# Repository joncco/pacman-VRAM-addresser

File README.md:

This is a reproduction of the VRAM Addresser board used in Midway's Pac-Man arcade PCB.

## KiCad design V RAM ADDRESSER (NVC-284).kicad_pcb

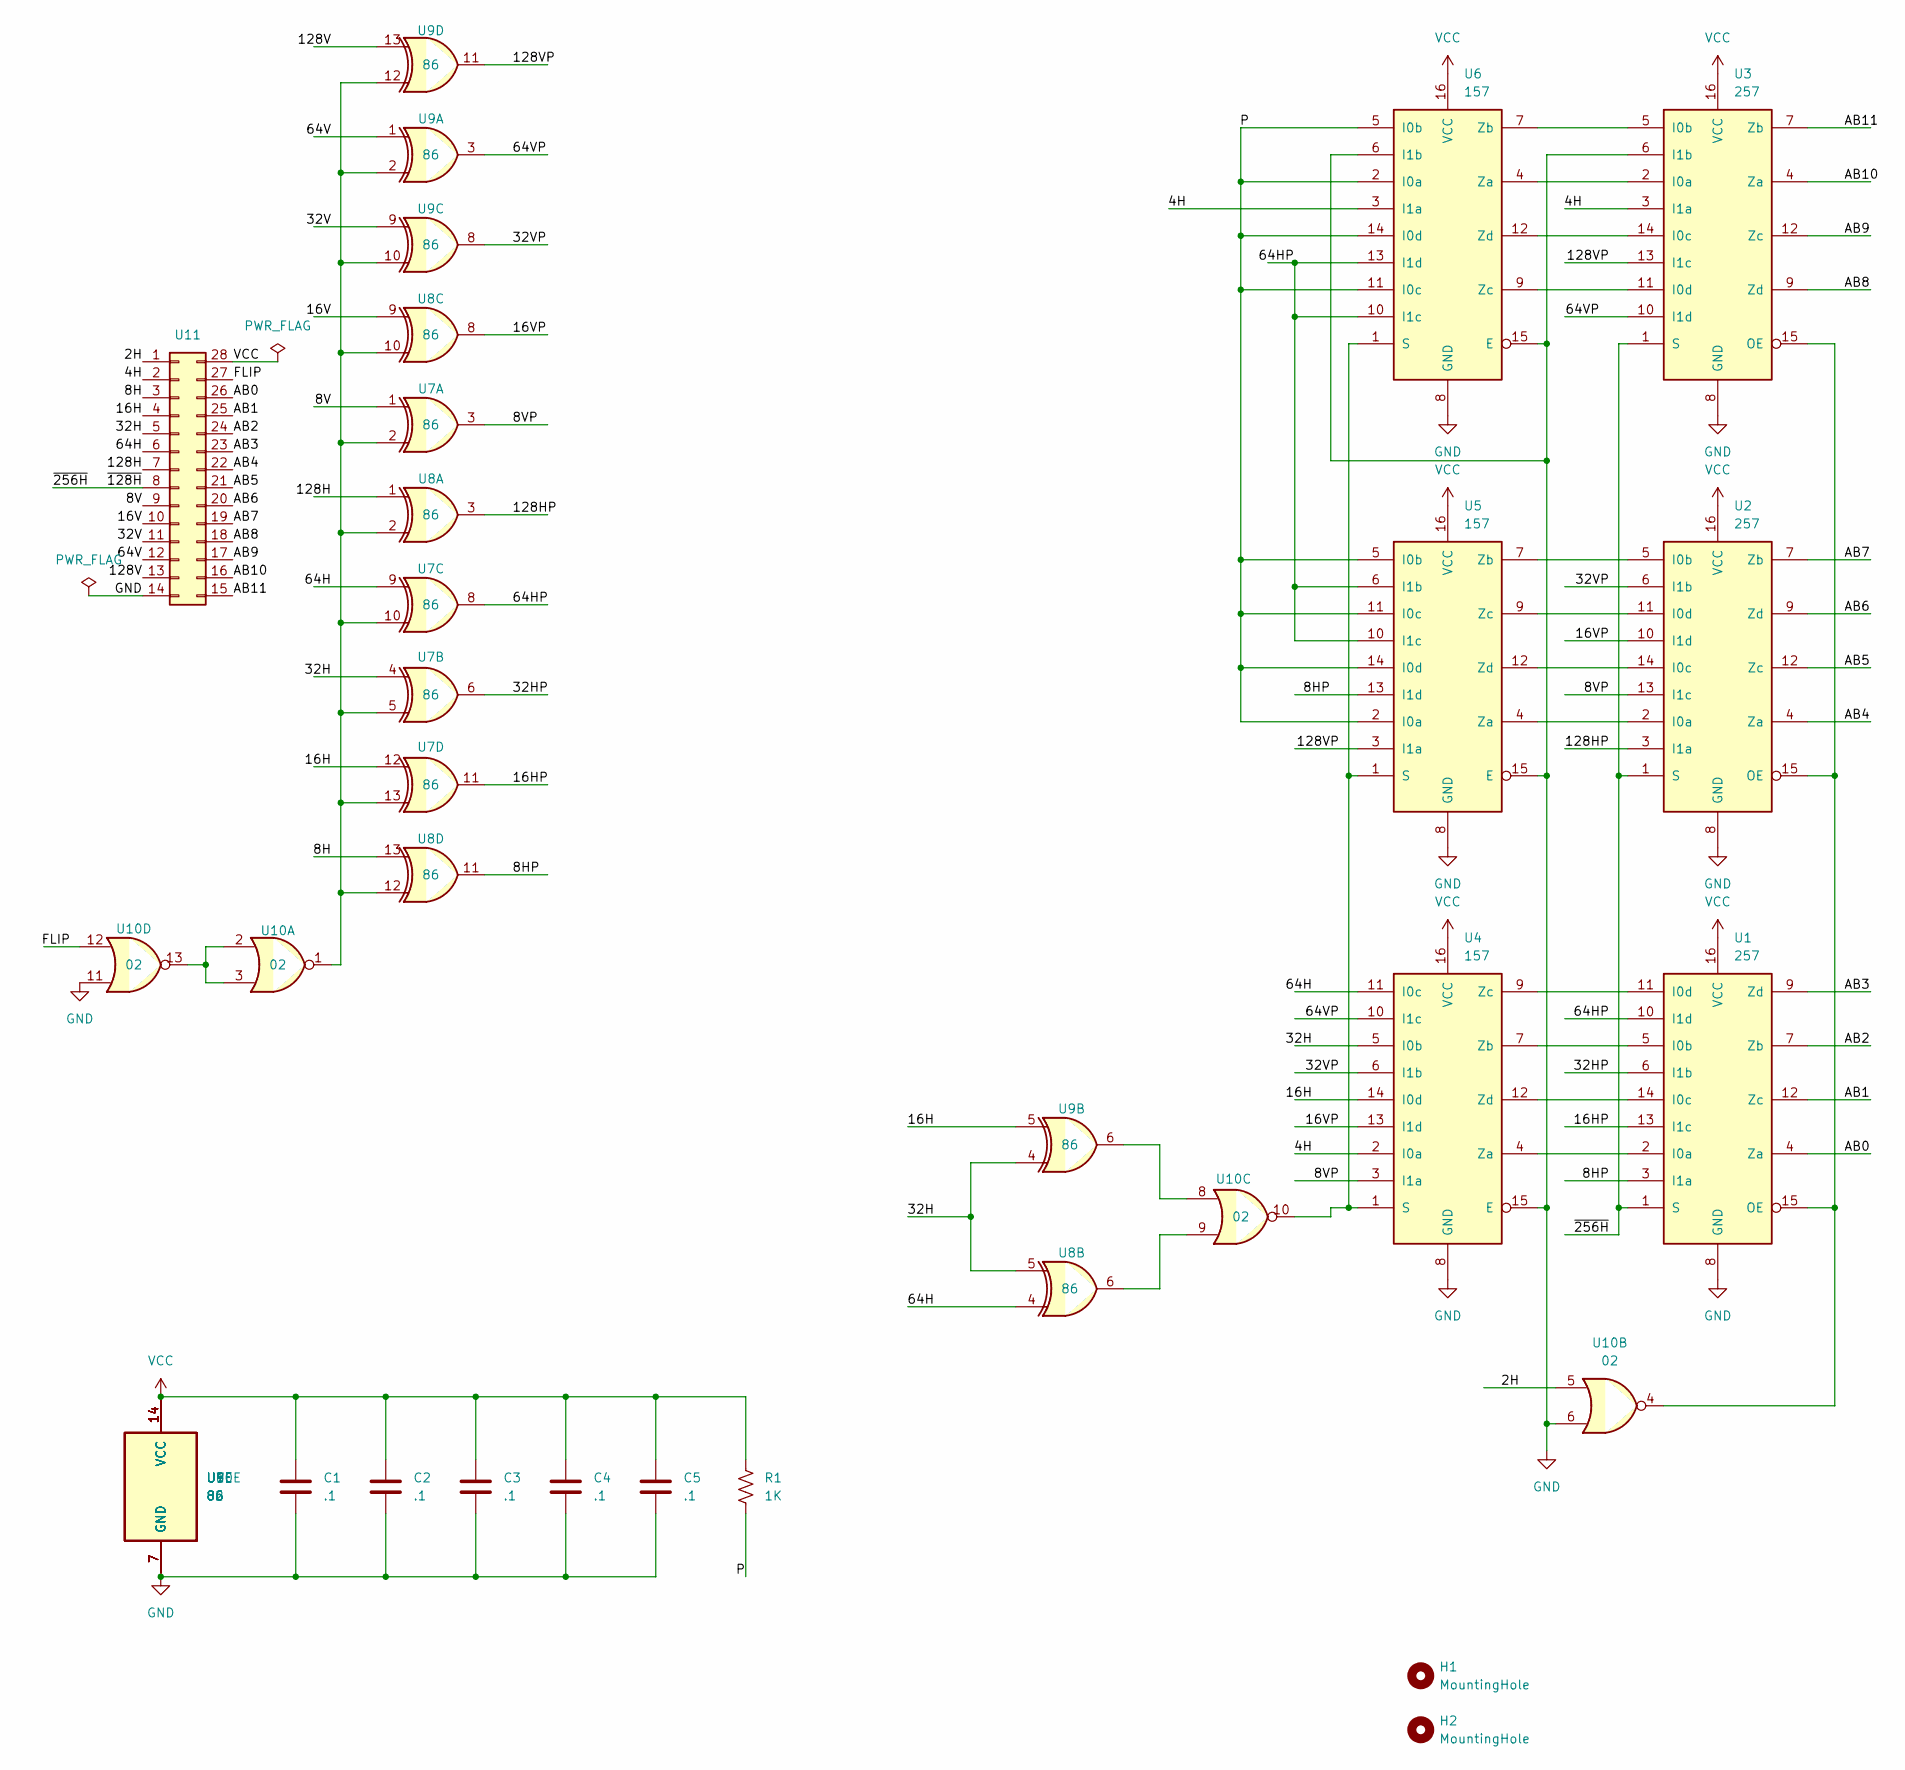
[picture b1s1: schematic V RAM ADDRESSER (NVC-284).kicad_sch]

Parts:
C1, C2, C3, C4, C5: .1; C_Rect_L9.0mm_W2.5mm_P10.16mm_MKT
H1, H2: MountingHole; MountingHole_3mm
R1: 1K; R_Axial_DIN0207_L6.3mm_D2.5mm_P10.16mm_Horizontal
U1, U2, U3: 257; DIP-16_W7.62mm_LongPads
U4, U5, U6: 157; DIP-16_W7.62mm_LongPads
U7, U8, U9: 86; DIP-14_W7.62mm_LongPads
U10: 02; DIP-14_W7.62mm_LongPads
U11: Conn_02x14_Counter_Clockwise; DIP-28_W15.24mm_LongPads

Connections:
/2H: U10.5, U11.1
/4H: U3.3 (I1a), U4.2 (I0a), U6.3 (I1a), U11.2
/8H: U8.13, U11.3
/8HP: U1.3 (I1a), U5.13 (I1d), U8.11
/8V: U7.1, U11.9
/8VP: U2.13 (I1c), U4.3 (I1a), U7.3
/16H: U4.14 (I0d), U7.12, U9.5, U11.4
/16HP: U1.13 (I1c), U7.11
/16V: U8.9, U11.10
/16VP: U2.10 (I1d), U4.13 (I1d), U8.8
/32H: U4.5 (I0b), U7.4, U8.5, U9.4, U11.5
/32HP: U1.6 (I1b), U7.6
/32V: U9.9, U11.11
/32VP: U2.6 (I1b), U4.6 (I1b), U9.8
/64H: U4.11 (I0c), U7.9, U8.4, U11.6
/64HP: U1.10 (I1d), U5.6 (I1b), U5.10 (I1c), U6.10 (I1c), U6.13 (I1d), U7.8
/64V: U9.1, U11.12
/64VP: U3.10 (I1d), U4.10 (I1c), U9.3
/128H: U8.1, U11.7
/128HP: U2.3 (I1a), U8.3
/128V: U9.13, U11.13
/128VP: U3.13 (I1c), U5.3 (I1a), U9.11
/AB0: U1.4 (Za), U11.26
/AB1: U1.12 (Zc), U11.25
/AB2: U1.7 (Zb), U11.24
/AB3: U1.9 (Zd), U11.23
/AB4: U2.4 (Za), U11.22
/AB5: U2.12 (Zc), U11.21
/AB6: U2.9 (Zd), U11.20
/AB7: U2.7 (Zb), U11.19
/AB8: U3.9 (Zd), U11.18
/AB9: U3.12 (Zc), U11.17
/AB10: U3.4 (Za), U11.16
/AB11: U3.7 (Zb), U11.15
/FLIP: U10.12, U11.27
/P: R1.2, U5.2 (I0a), U5.5 (I0b), U5.11 (I0c), U5.14 (I0d), U6.2 (I0a), U6.5 (I0b), U6.11 (I0c), U6.14 (I0d)
/~128H: U1.1 (S), U2.1 (S), U3.1 (S), U11.8
GND: C1.2, C2.2, C3.2, C4.2, C5.2, U1.8 (GND), U2.8 (GND), U3.6 (I1b), U3.8 (GND), U4.8 (GND), U4.15 (E), U5.8 (GND), U5.15 (E), U6.6 (I1b), U6.8 (GND), U6.15 (E), U7.7 (GND), U8.7 (GND), U9.7 (GND), U10.6, U10.7 (GND), U10.11, U11.14
unnamed: U1.2 (I0a), U4.4 (Za)
unnamed: U1.5 (I0b), U4.7 (Zb)
unnamed: U1.14 (I0c), U4.12 (Zd)
unnamed: U1.11 (I0d), U4.9 (Zc)
unnamed: U1.15 (OE), U2.15 (OE), U3.15 (OE), U10.4
unnamed: U2.2 (I0a), U5.4 (Za)
unnamed: U2.5 (I0b), U5.7 (Zb)
unnamed: U2.14 (I0c), U5.12 (Zd)
unnamed: U2.11 (I0d), U5.9 (Zc)
unnamed: U3.2 (I0a), U6.4 (Za)
unnamed: U3.5 (I0b), U6.7 (Zb)
unnamed: U3.14 (I0c), U6.12 (Zd)
unnamed: U3.11 (I0d), U6.9 (Zc)
unnamed: U4.1 (S), U5.1 (S), U6.1 (S), U10.10
unnamed: U7.2, U7.5, U7.10, U7.13, U8.2, U8.10, U8.12, U9.2, U9.10, U9.12, U10.1
unnamed: U9.6, U10.8
unnamed: U8.6, U10.9
unnamed: U10.2, U10.3, U10.13
VCC: C1.1, C2.1, C3.1, C4.1, C5.1, R1.1, U1.16 (VCC), U2.16 (VCC), U3.16 (VCC), U4.16 (VCC), U5.16 (VCC), U6.16 (VCC), U7.14 (VCC), U8.14 (VCC), U9.14 (VCC), U10.14 (VCC), U11.28

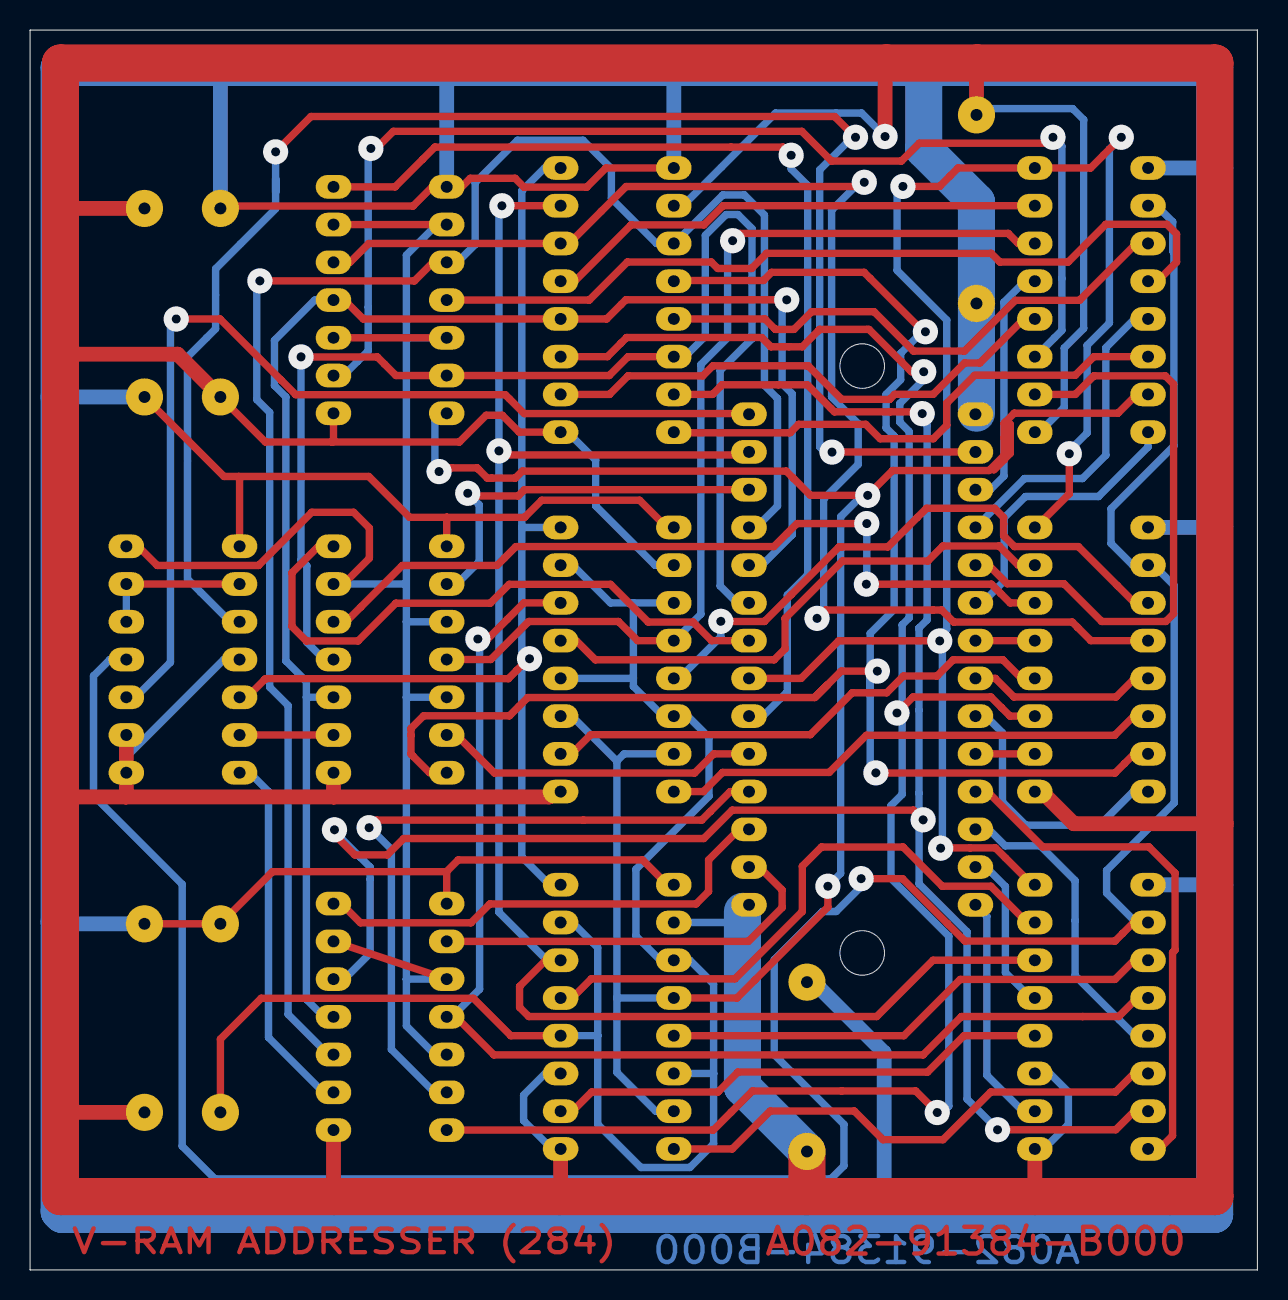
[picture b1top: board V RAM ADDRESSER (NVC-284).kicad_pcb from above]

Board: 2 copper layers, 82.6 x 83.5 mm, 19 parts (0 on the bottom side), 57 nets.

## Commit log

2024-12-12 Add CC-BY-4.0
